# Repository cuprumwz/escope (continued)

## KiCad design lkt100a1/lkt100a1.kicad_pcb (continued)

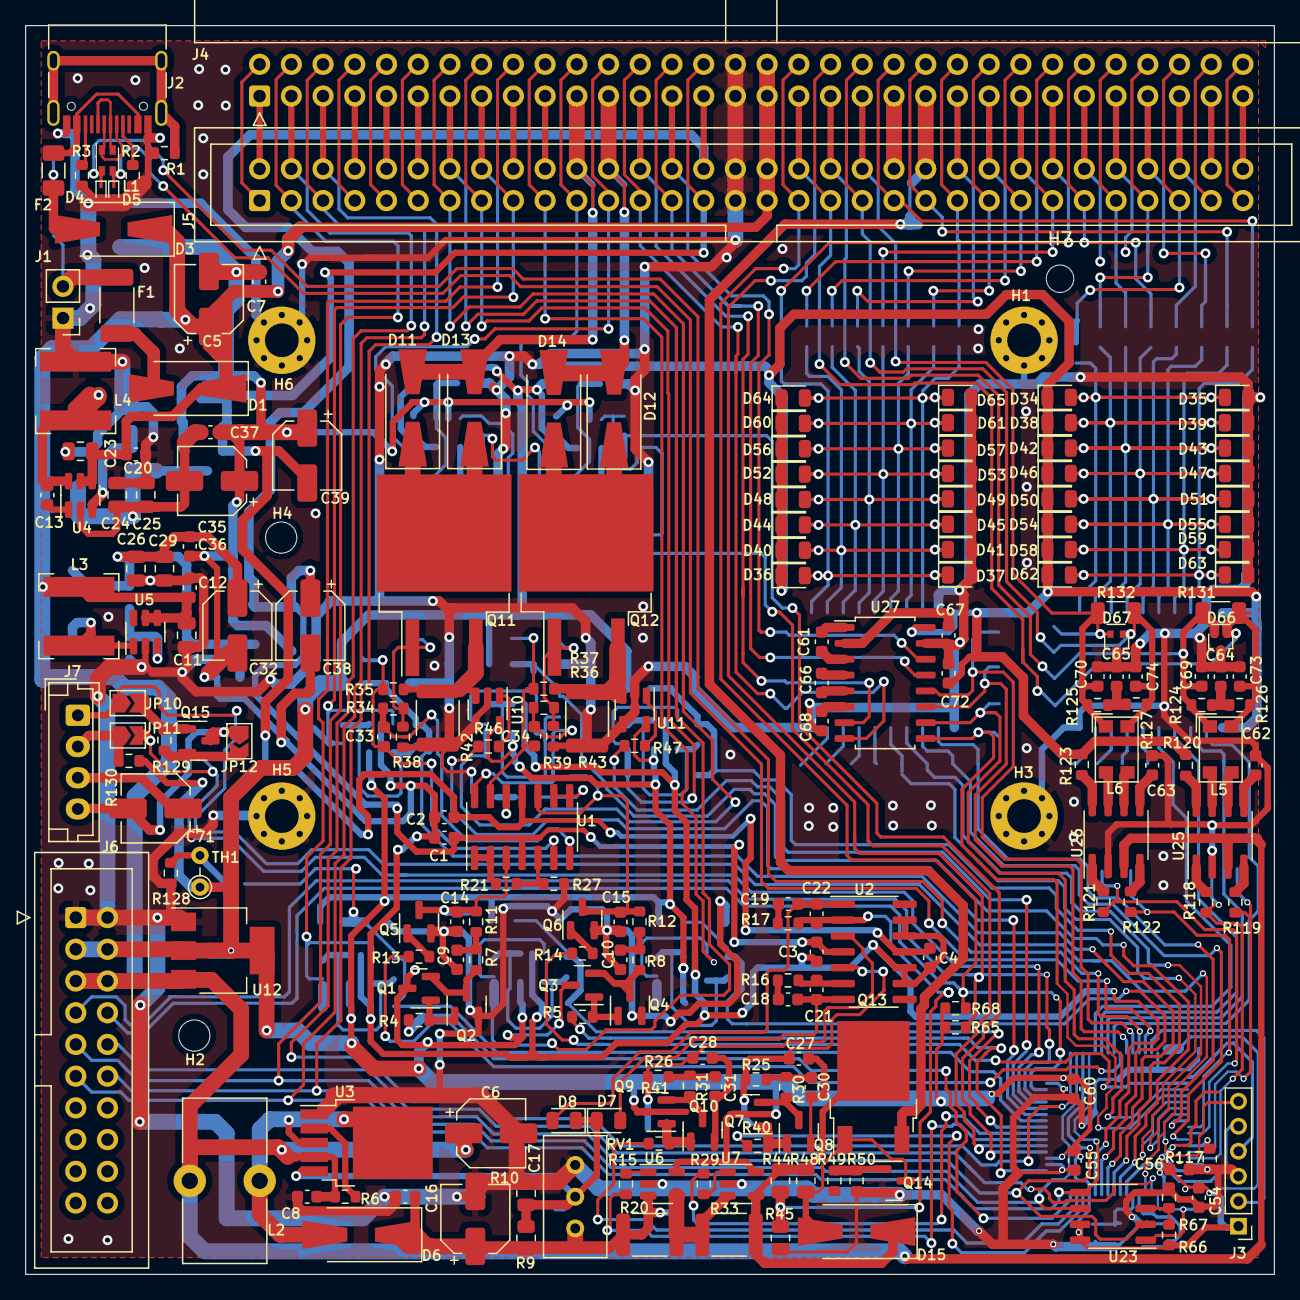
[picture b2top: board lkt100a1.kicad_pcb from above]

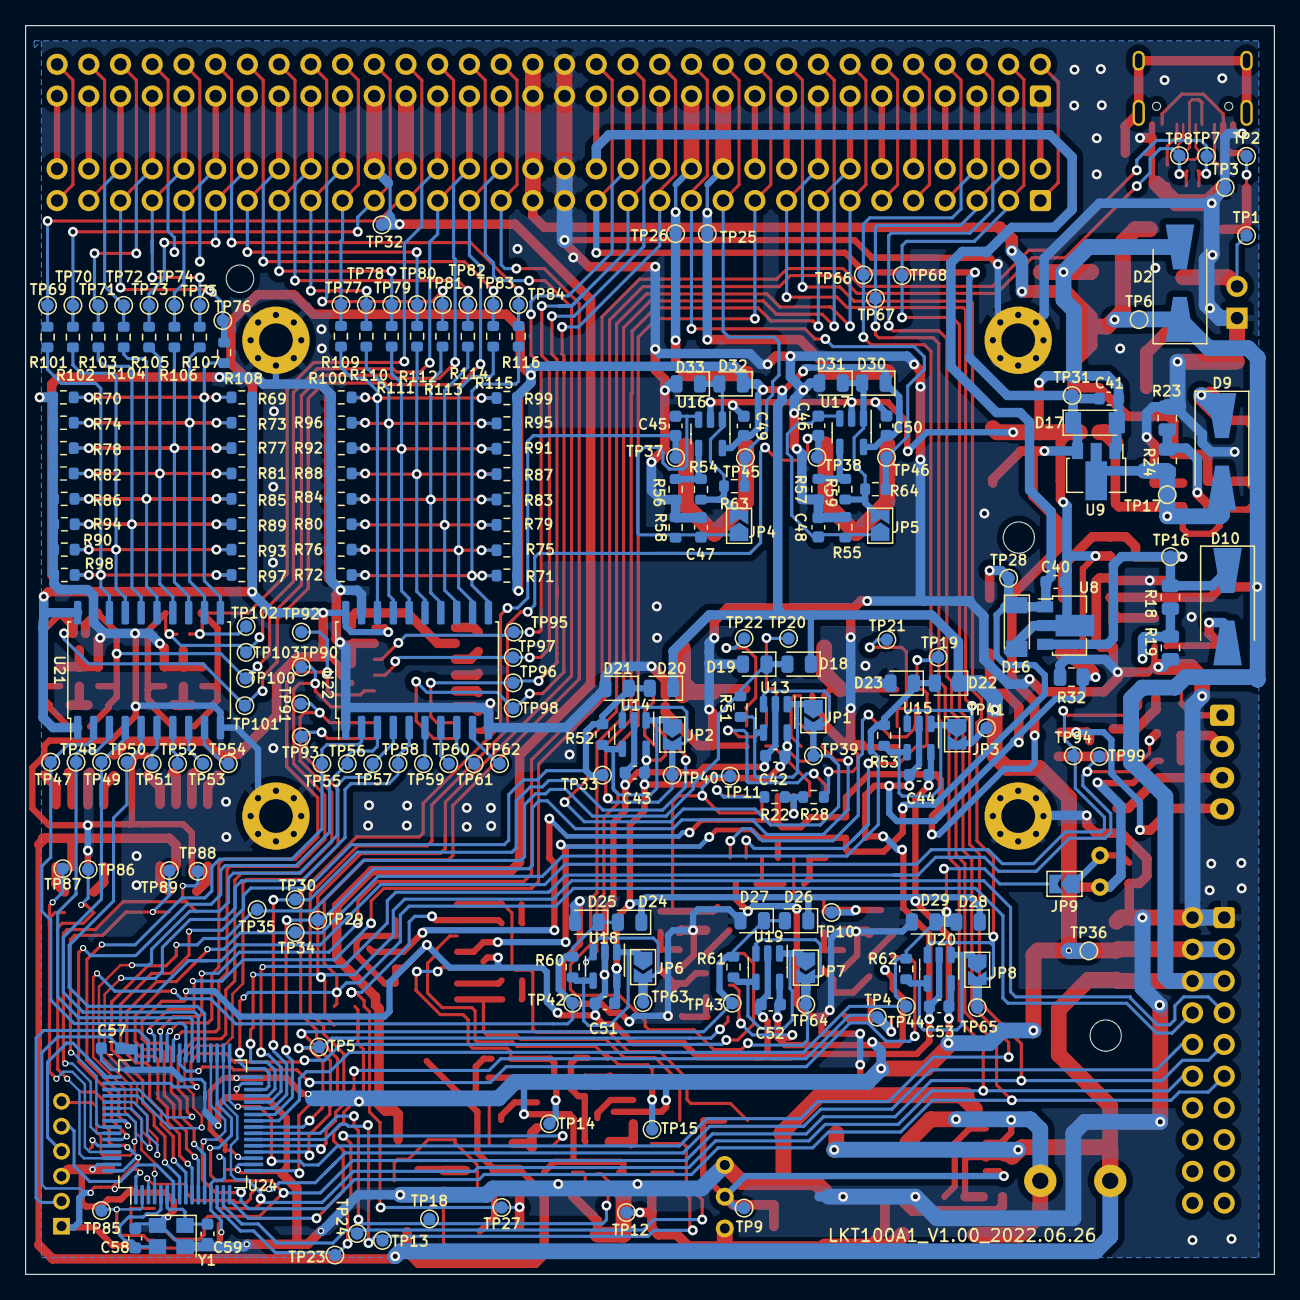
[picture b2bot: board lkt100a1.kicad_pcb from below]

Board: 2 copper layers, 100.0 x 100.0 mm, 455 parts (233 on the bottom side), 242 nets.

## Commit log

2023-02-20 init
2023-02-20 add ignore file -backups
